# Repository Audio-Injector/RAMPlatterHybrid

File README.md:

# RAM Platter Hybrid

Hybrid software / hardware DJ kit

The RAM Platter Hybrid is a hardware and software to allow digital DJing of your music.

The system implements speed change resampling in hardware. The software provides the interface and controls the audio (direction) and other signal processing.

By performing resampling in hardware, the majority of the core signal processing does not burden the CPU. This allows the system to run on low power devices. It should also allow the system latency (time lag between moving the record and hearing it move) to be reduced.

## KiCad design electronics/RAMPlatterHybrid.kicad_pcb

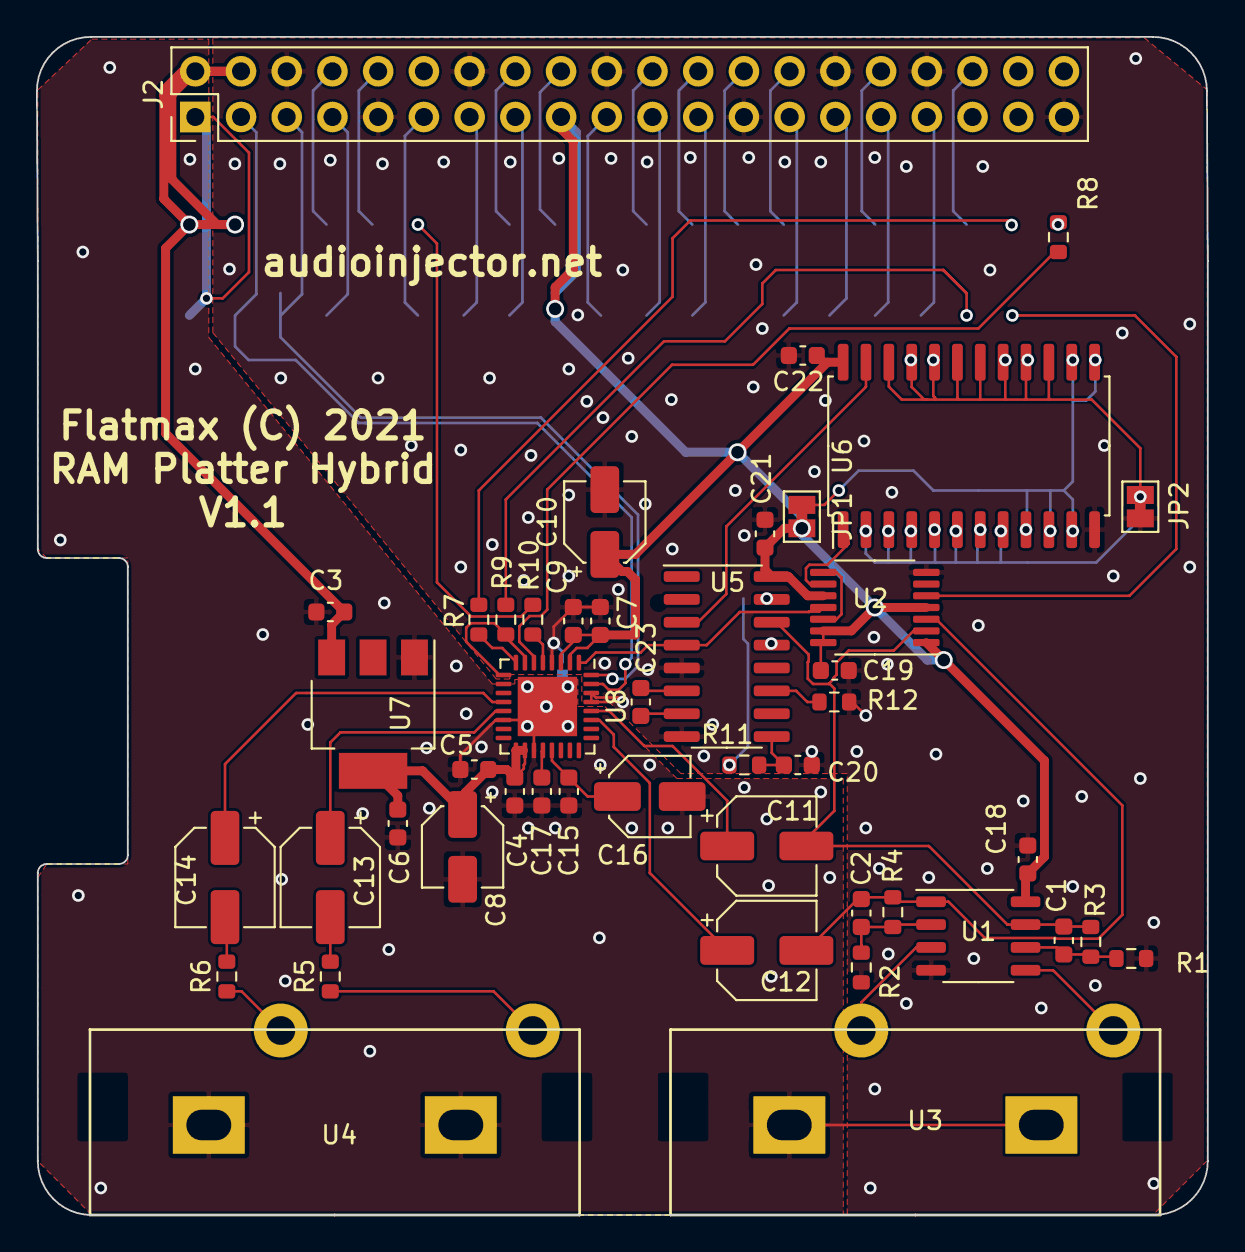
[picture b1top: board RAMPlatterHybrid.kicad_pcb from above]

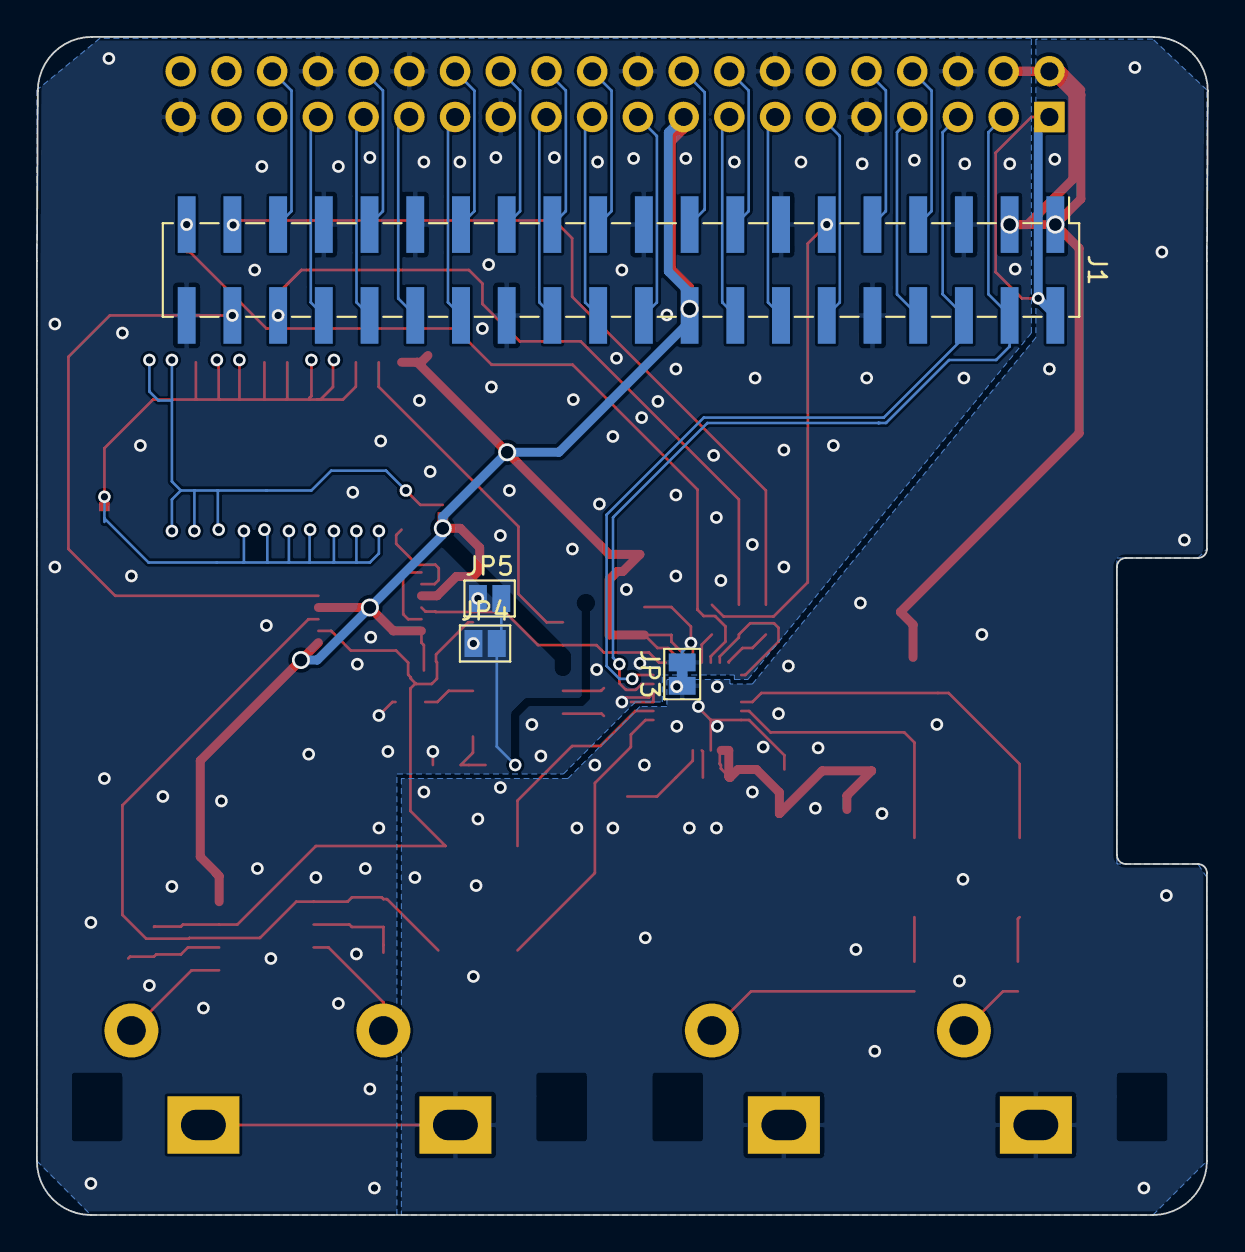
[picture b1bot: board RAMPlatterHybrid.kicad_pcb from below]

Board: 2 copper layers, 65.1 x 65.5 mm, 50 parts (4 on the bottom side), 67 nets.

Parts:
C1, C2, C20: 2.5n; C_0603_1608Metric
C3, C4, C5, C6, C7, C9, C15, C17, C18, C19, C21, C22: 100n; C_0603_1608Metric
C8, C10, C16: 10u; CP_Elec_4x5.3
C11, C12, C13, C14: 1u NP; CP_Elec_5x5.3
C23: 1n; C_0603_1608Metric
J1: Raspberry_Pi_2_3; 02x20.SMD.pinLocsRev
J2: Raspberry_Pi_2_3; PinHeader_2x20_P2.54mm_Vertical
JP1, JP2, JP3: SolderJumper_2_Bridged; SolderJumper-2_P1.3mm_Bridged_Pad1.0x1.5mm
JP4, JP5: Jumper_2_Open; SolderJumper-2_P1.3mm_Open_Pad1.0x1.5mm
R1, R2: 20R; R_0603_1608Metric
R3, R4, R11: 10k; R_0603_1608Metric
R5, R6: 100R; R_0603_1608Metric
R7, R8, R9, R10: 75R; R_0603_1608Metric
R12: 3k; R_0603_1608Metric
U1: LM358; SOP-8_3.9x4.9mm_P1.27mm
U2: 74LVC74APW; TSSOP-14_4.4x5mm_P0.65mm
U3, U4: AV2-8.4-10
U5: HC4046A; SOP-16_3.9x9.9mm_P1.27mm
U6: CD74HC4059; SOIC-24W_7.5x15.4mm_P1.27mm
U7: AP1117-33; SOT-223-3_TabPin2
U8: WM8750; QFN-32-1EP_5x5mm_P0.5mm_EP3.3x3.3mm

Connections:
+3V3: C7.1, C9.1, C10.1, C18.2, C19.1, C21.1, C22.1, J1.17, J2.17, JP1.1, U1.8, U2.1, U2.4, U2.10, U2.13, U2.14, U5.16, U6.24, U8.2, U8.3
+5V: C3.1, J1.2, J1.4, J2.2, J2.4, U7.3
/AVDD: C4.1, C5.1, C6.1, C8.1, U7.2, U8.17, U8.18
/HIGH: JP1.2, U6.9, U6.10, U6.11, U6.13, U6.14
/I2S_ADC: J1.38, R7.2
/I2S_BCLK: J1.12, R10.2
/I2S_DAC: J1.40, R8.2
/I2S_LRCLK: J1.35, R9.2
/LOW: JP2.2, U6.2, U6.3, U6.4, U6.5, U6.6, U6.7, U6.8, U6.15, U6.16, U6.17, U6.18, U6.19, U6.20, U6.21, U6.22
/LRCAIn: U1.5, U3.2
/LRCAOut: R5.1, U4.2
/Lin: C1.1, C11.2, R3.1, U1.7, U2.2, U5.14
/MCLK: U2.11, U5.4, U8.1
/MCLKo2: U2.9, U6.1
/MCLKo1200: U5.3, U6.23
/RRCAIn: U1.3, U3.4
/RRCAOut: R6.1, U4.4
/Rin: C2.1, C12.2, R4.1, U1.1, U2.3
/SCL: J1.5, J2.5, U8.32
/SDA: J1.3, J2.3, U8.31
/direction: J1.37, U2.5
GND: C7.2, C9.2, C10.2, C18.1, C19.2, C20.1, C21.2, C22.2, J1.6, J1.9, J1.14, J1.20, J1.25, J1.30, J1.34, J1.39, J2.6, J2.9, J2.14, J2.20, J2.25, J2.30, J2.34, J2.39, JP2.1, JP3.2, R1.1, R2.1, R12.2, U1.4, U2.7, U5.5, U5.8, U6.12, U8.4, U8.29, U8.30
GNDA: C3.2, C4.2, C5.2, C6.2, C8.2, C15.2, C16.2, C17.2, JP3.1, U3.1, U3.3, U4.1, U4.3, U7.1, U8.14, U8.19, U8.33
unnamed: C1.2, R1.2, R3.2, U1.6
unnamed: C2.2, R2.2, R4.2, U1.2
unnamed: C11.1, U8.28
unnamed: C12.1, U8.27
unnamed: C13.1, U8.13
unnamed: C13.2, R5.2
unnamed: C14.1, U8.12
unnamed: C14.2, R6.2
unnamed: C15.1, C16.1, U8.21
unnamed: C17.1, U8.20
unnamed: C20.2, R11.2, U5.9
unnamed: C23.1, U5.6
unnamed: C23.2, U5.7
unnamed: J1.1, J2.1
unnamed: J1.7, J2.7
unnamed: J1.8, J2.8
unnamed: J1.10, J2.10
unnamed: J1.11, J2.11
unnamed: J1.13, J2.13
unnamed: J1.15, J2.15
unnamed: J1.16, J2.16
unnamed: J1.18, J2.18
unnamed: J1.19, J2.19
unnamed: J1.21, J2.21
unnamed: J1.22, J2.22
unnamed: J1.23, J2.23
unnamed: J1.24, J2.24
unnamed: J1.26, J2.26
unnamed: J1.27, J2.27
unnamed: J1.28, J2.28
unnamed: J1.29, J2.29
unnamed: J1.31, J2.31
unnamed: J1.32, J2.32
unnamed: J1.33, J2.33
unnamed: J1.36, J2.36
unnamed: JP4.1, U5.13
unnamed: JP4.2, JP5.2, R11.1
unnamed: JP5.1, U5.15
unnamed: R7.1, U8.8
unnamed: R8.1, U8.6
unnamed: R9.1, U8.7, U8.9
unnamed: R10.1, U8.5
unnamed: R12.1, U5.11
unnamed: U2.8, U2.12

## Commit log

2018-01-11 Initial commit with a building test C++ system.
2018-01-14 Stripped back to a pure C++ project foundation.
2020-07-14 First working swig version
2020-07-16 updated the readme
2021-11-13 began layout
2021-11-16 changed to a 600 divider.
2021-11-16 v1.0
2021-11-16 Added gerbers
2021-11-24 moved code related files into the software directory
2021-11-24 License update
2021-11-24 Configure now looks for the Eigen and gtkIOStream packages.
2021-11-24 Added the RAMPlatterDebug class.
2021-11-24 Created the libRAMPlatterHybrid library and the Audio class which will handle Audio
2021-11-24 Got rid of old test source code
2021-11-24 Renamed Audio::loadAudio to Audio::loadFile. Got rid of some spurious code.
2021-11-24 configure looks for a different header file.
2021-11-24 declare the existance of Audio<int>
2021-11-24 New class PlatterAudio which handles fwd and rev audio direct from RAM
2021-11-24 Update swig to use PlatterAudio
2021-11-24 Audio inherits publicly
2021-11-24 PlatterAudio::loadFile now loads the reversed audio into audioRev
2021-11-24 Updated swig
2021-11-24 PlatterAudio fix audio reversal
2021-11-24 PlatterAudioTest.C dumps reversed audio to disk for testing.
2021-11-25 added Audio::n the index into the audio
2021-11-25 Began implementing PlatterALSA.H
2021-11-26 PlatterALSA now opening and setting up the audio device.
2021-11-26 Simplify PlatterALSA a little.
2021-11-26 More simplifications for PlatterALSA.C
2021-11-26 error checking on Playback::open
2021-11-26 Handling periods more correctly now.
2021-11-26 test Makefile use AM_CPPLAGS
2021-11-26 PlatterALSA::play setup to play
2021-11-26 Make matrices row major
2021-11-26 set nonblocking and change test conditions
2021-11-26 Simplify playback to only use pointers, not Eigen method calls.
2021-11-26 Add 96 kHz sample rate capability.
2021-12-06 v1.1 Many hardware bug fixes, 4059 now dividing correctly. 4046 voc on better target, still debugging 4046 PLL.
2021-12-06 addd RCA symbol and footprint
2021-12-06 added a pdf
2022-03-04 added a figure for the wiki
2022-03-04 added another fig for the wiki
2022-03-04 added a wiki link to the new required hardware to the sch file.

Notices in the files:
electronics/RAMPlatterHybrid.kicad_pcb:
Flatmax (C) 2021
